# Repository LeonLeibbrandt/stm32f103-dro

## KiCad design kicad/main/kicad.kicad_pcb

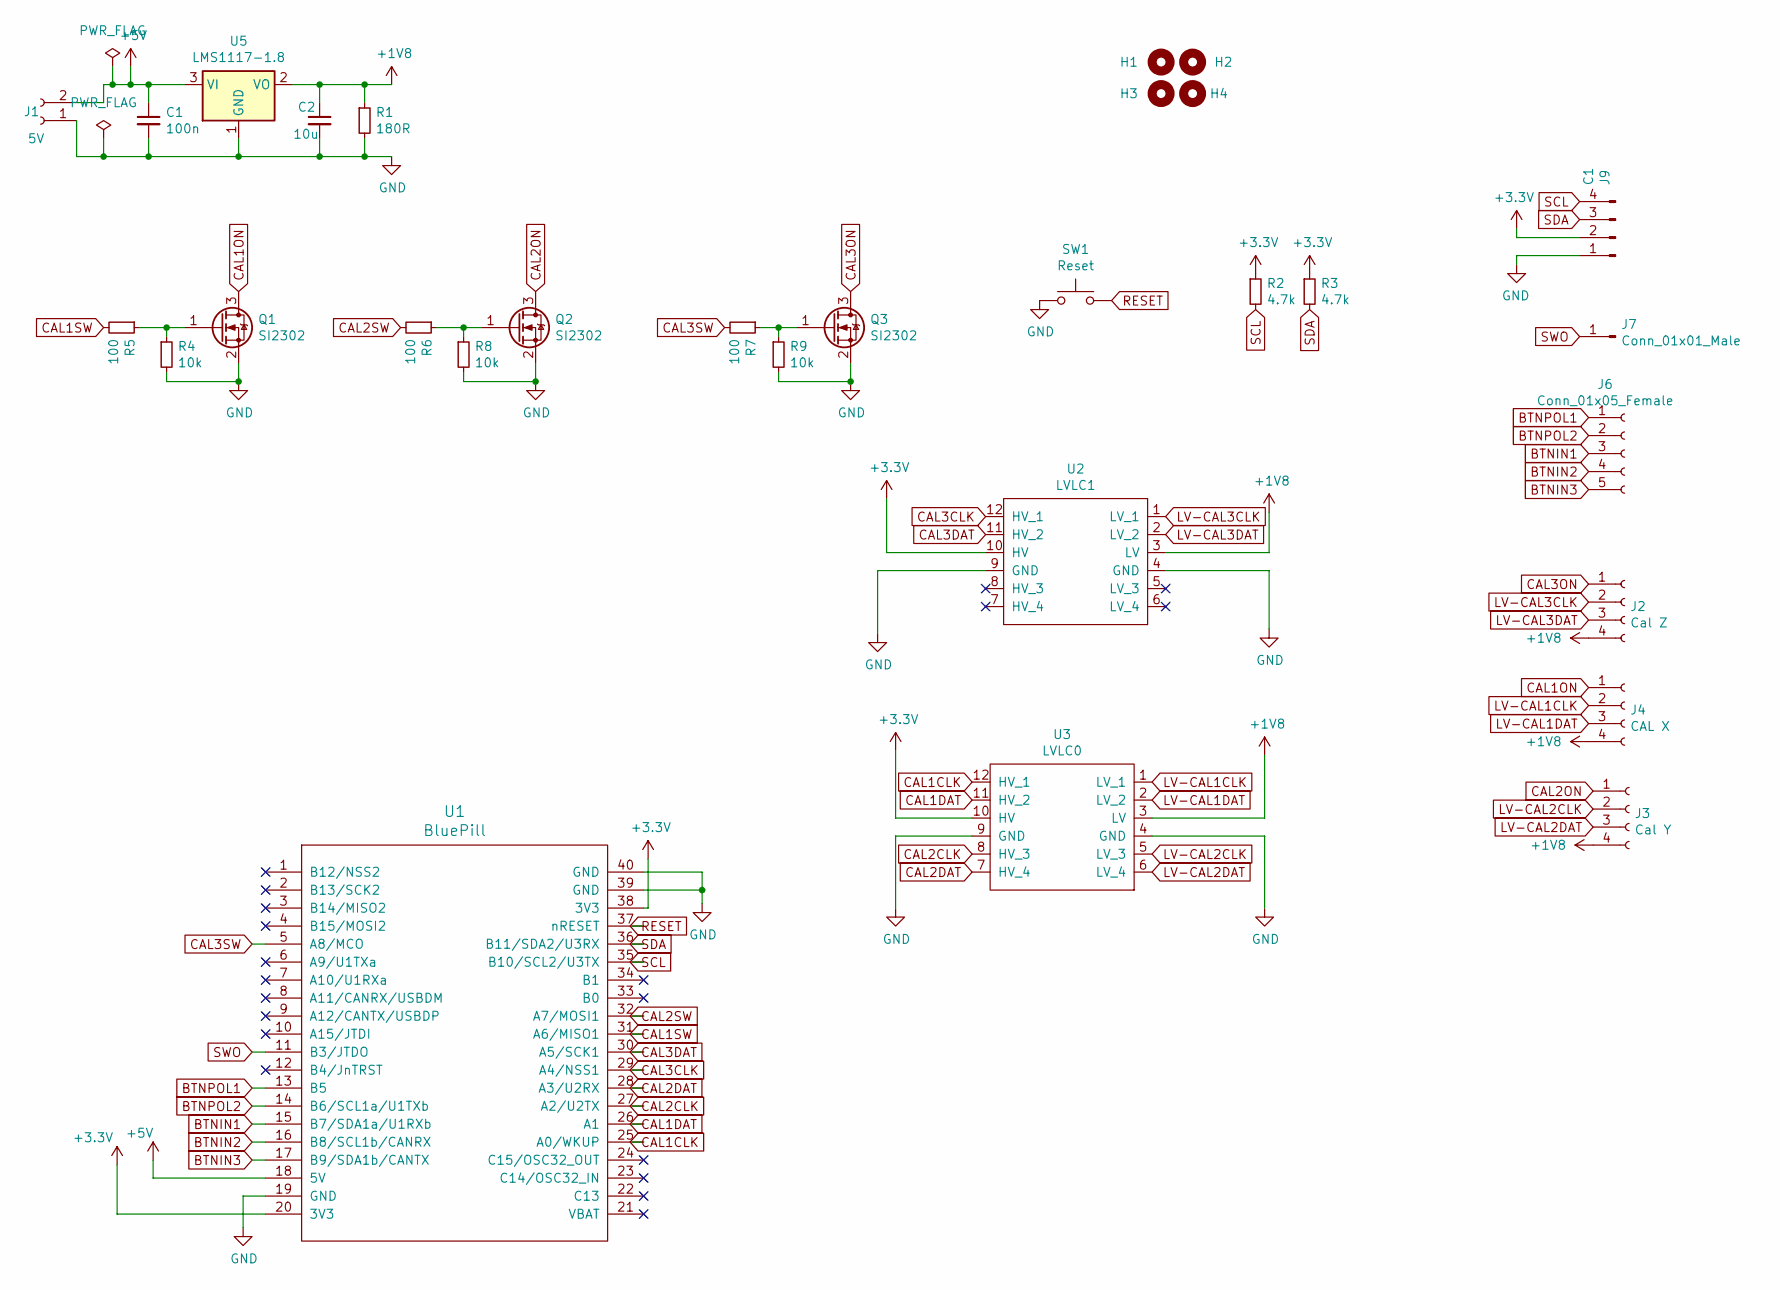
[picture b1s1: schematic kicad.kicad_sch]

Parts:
C1: 100n; C_1206_3216Metric
C2: 10u; C_1206_3216Metric
H1, H2, H3, H4: MountingHole; MountingHole_3.5mm_Pad
J1: 5V; JST_XH_B2B-XH-A_1x02_P2.50mm_Vertical
J2: Cal Z; JST_XH_B4B-XH-A_1x04_P2.50mm_Vertical
J3: Cal Y; JST_XH_B4B-XH-A_1x04_P2.50mm_Vertical
J4: CAL X; JST_XH_B4B-XH-A_1x04_P2.50mm_Vertical
J6: Conn_01x05_Female; JST_XH_B5B-XH-A_1x05_P2.50mm_Vertical
J7: Conn_01x01_Male; PinHeader_1x01_P2.54mm_Horizontal
J9: C1; JST_XH_B4B-XH-A_1x04_P2.50mm_Vertical
Q1, Q2, Q3: SI2302; SOT-23
R1: 180R; R_1206_3216Metric
R2, R3: 4.7k; R_1206_3216Metric
R4, R8, R9: 10k; R_1206_3216Metric
R5, R6, R7: 100; R_1206_3216Metric
SW1: Reset; PinHeader_1x02_P2.54mm_Vertical
U1: BluePill; bluepill
U2: LVLC1; levelconverter
U3: LVLC0; levelconverter
U5: LMS1117-1.8; SOT-223-3_TabPin2

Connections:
+1V8: C2.1, J2.4, J3.4, J4.4, R1.1, U2.3 (LV), U3.3 (LV), U5.2 (VO)
+3V3: J9.2, R2.1, R3.1, U1.20 (3V3), U1.38 (3V3), U2.10 (HV), U3.10 (HV)
+5V: C1.1, J1.2, U1.18 (5V), U5.3 (VI)
BTNIN1: J6.3, U1.15 (B7/SDA1a/U1RXb)
BTNIN2: J6.4, U1.16 (B8/SCL1b/CANRX)
BTNIN3: J6.5, U1.17 (B9/SDA1b/CANTX)
BTNPOL1: J6.1, U1.13 (B5)
BTNPOL2: J6.2, U1.14 (B6/SCL1a/U1TXb)
CAL1CLK: U1.25 (A0/WKUP), U3.12 (HV_1)
CAL1DAT: U1.26 (A1), U3.11 (HV_2)
CAL1ON: J4.1, Q1.3 (D)
CAL1SW: R5.2, U1.31 (A6/MISO1)
CAL2CLK: U1.27 (A2/U2TX), U3.8 (HV_3)
CAL2DAT: U1.28 (A3/U2RX), U3.7 (HV_4)
CAL2ON: J3.1, Q2.3 (D)
CAL2SW: R6.2, U1.32 (A7/MOSI1)
CAL3CLK: U1.29 (A4/NSS1), U2.12 (HV_1)
CAL3DAT: U1.30 (A5/SCK1), U2.11 (HV_2)
CAL3ON: J2.1, Q3.3 (D)
CAL3SW: R7.2, U1.5 (A8/MCO)
GND: C1.2, C2.2, J1.1, J9.1, Q1.2 (S), Q2.2 (S), Q3.2 (S), R1.2, R4.2, R8.2, R9.2, SW1.1, U1.19 (GND), U1.39 (GND), U1.40 (GND), U2.4 (GND), U2.9 (GND), U3.4 (GND), U3.9 (GND), U5.1 (GND)
LV-CAL1CLK: J4.2, U3.1 (LV_1)
LV-CAL1DAT: J4.3, U3.2 (LV_2)
LV-CAL2CLK: J3.2, U3.5 (LV_3)
LV-CAL2DAT: J3.3, U3.6 (LV_4)
LV-CAL3CLK: J2.2, U2.1 (LV_1)
LV-CAL3DAT: J2.3, U2.2 (LV_2)
unnamed: Q1.1 (G), R4.1, R5.1
unnamed: Q2.1 (G), R6.1, R8.1
unnamed: Q3.1 (G), R7.1, R9.1
RESET: SW1.2, U1.37 (nRESET)
SCL: J9.4, R2.2, U1.35 (B10/SCL2/U3TX)
SDA: J9.3, R3.2, U1.36 (B11/SDA2/U3RX)
SWO: J7.1, U1.11 (B3/JTDO)

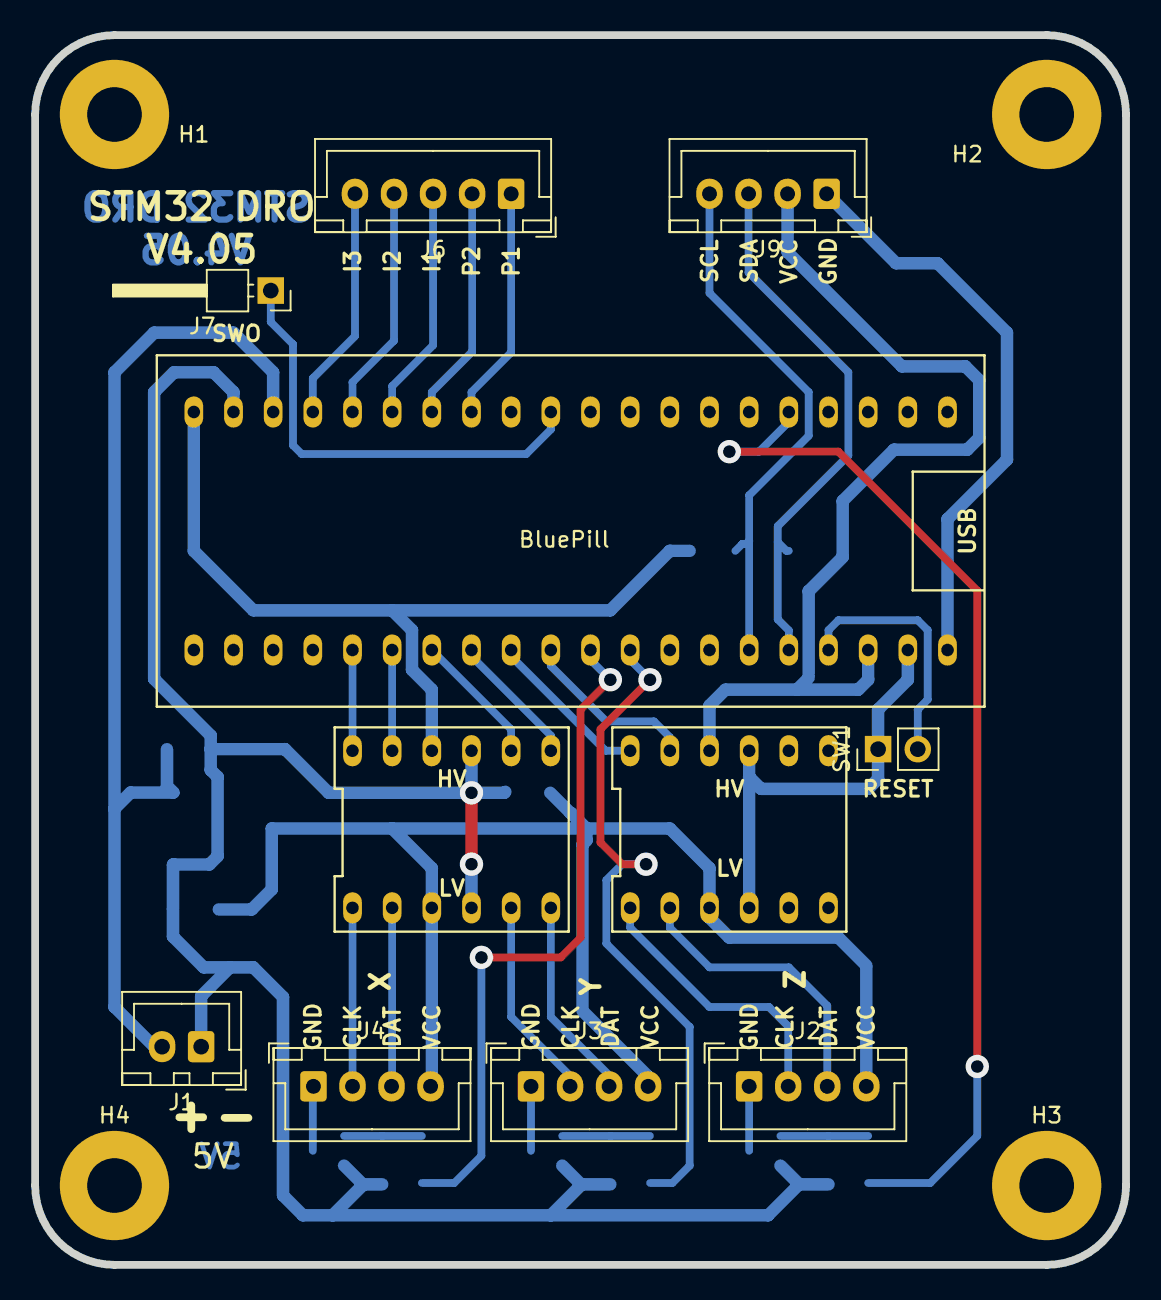
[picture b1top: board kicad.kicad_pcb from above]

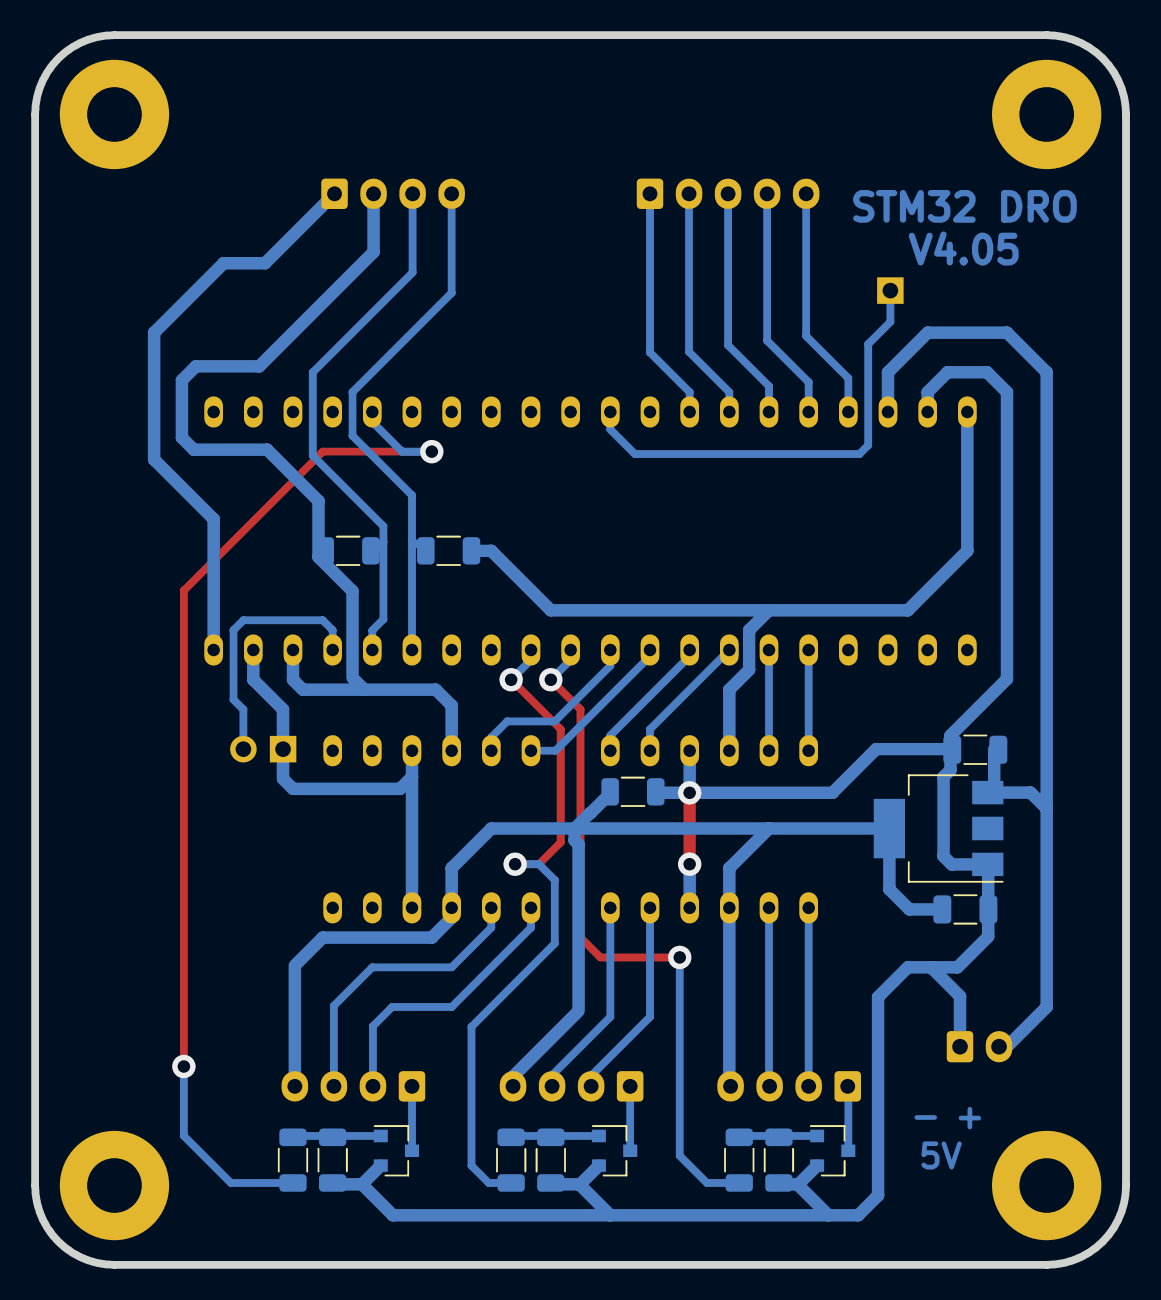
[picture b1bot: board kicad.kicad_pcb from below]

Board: 2 copper layers, 69.8 x 78.7 mm, 30 parts (15 on the bottom side), 34 nets.

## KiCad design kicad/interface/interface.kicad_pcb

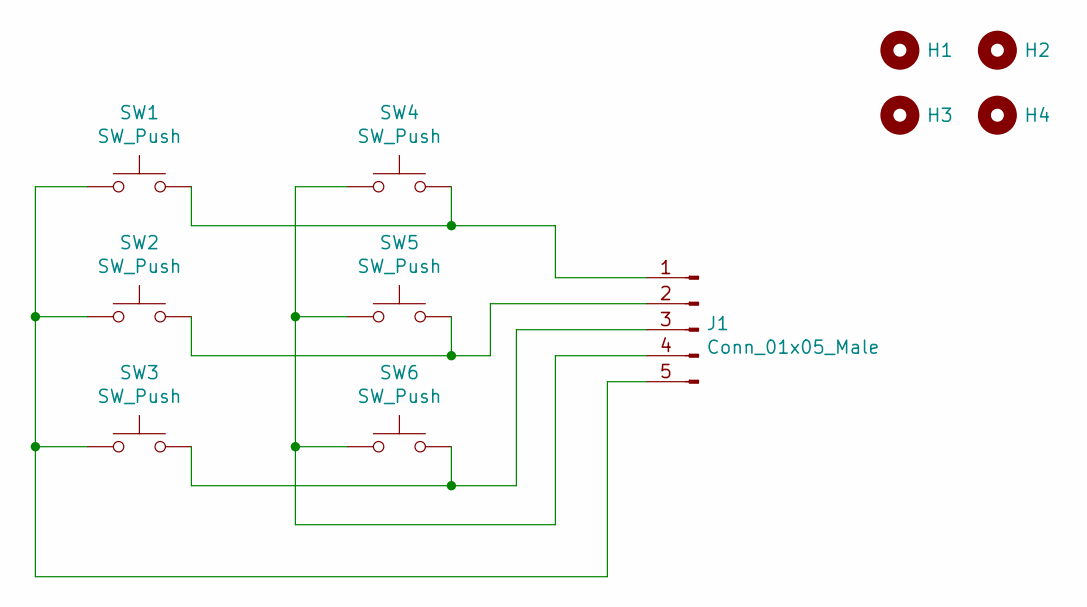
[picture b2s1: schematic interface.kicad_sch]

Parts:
H1, H2, H3, H4: MountingHole; MountingHole_3mm_Pad
J1: Conn_01x05_Male; JST_XH_B5B-XH-A_1x05_P2.50mm_Vertical
SW1, SW2, SW3, SW4, SW5, SW6: SW_Push; SW_PUSH-12mm

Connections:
unnamed: J1.1, SW1.2, SW4.2
unnamed: J1.2, SW2.2, SW5.2
unnamed: J1.3, SW3.2, SW6.2
unnamed: J1.4, SW4.1, SW5.1, SW6.1
unnamed: J1.5, SW1.1, SW2.1, SW3.1

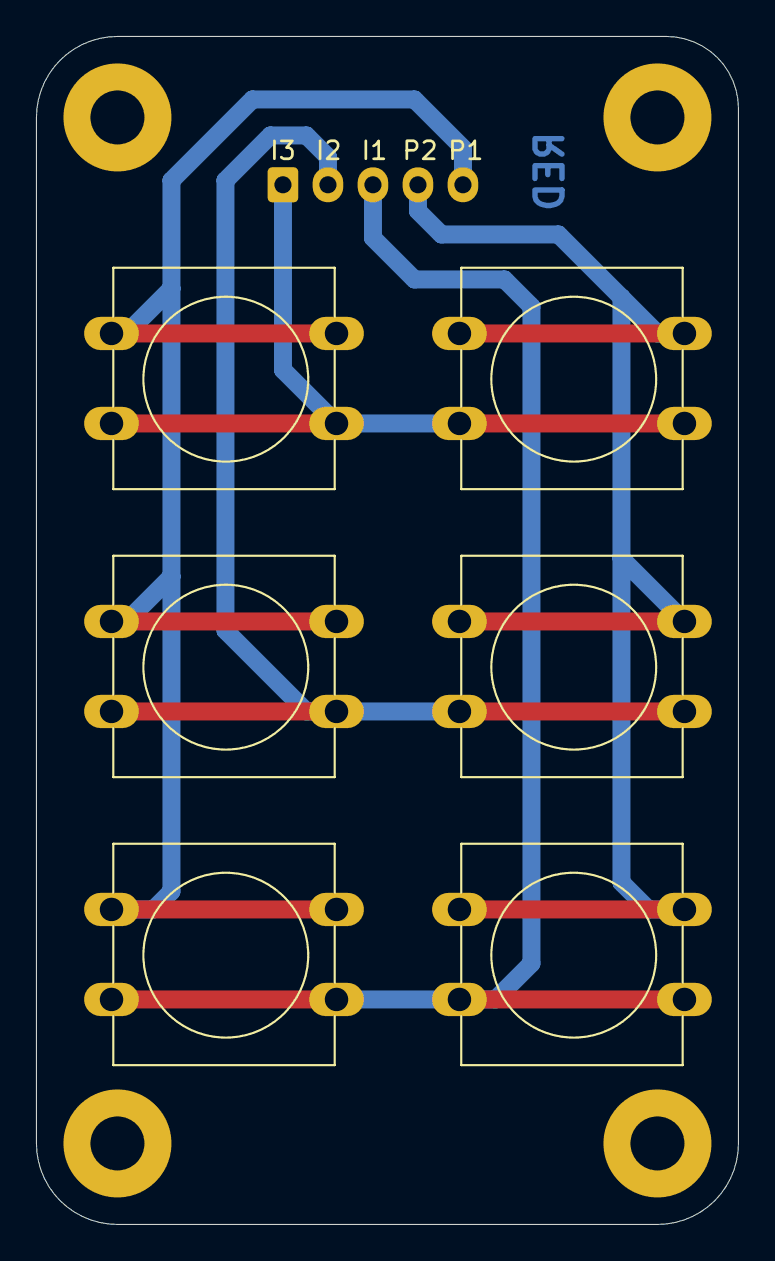
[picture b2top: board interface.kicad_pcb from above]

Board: 2 copper layers, 39.0 x 66.0 mm, 11 parts (1 on the bottom side), 5 nets.

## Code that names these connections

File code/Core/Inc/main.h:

/* USER CODE BEGIN Header */
/**
  ******************************************************************************
  * @file           : main.h
  * @brief          : Header for main.c file.
  *                   This file contains the common defines of the application.
  ******************************************************************************
  * @attention
  *
  * <h2><center>&copy; Copyright (c) 2020 STMicroelectronics.
  * All rights reserved.</center></h2>
  *
  * This software component is licensed by ST under BSD 3-Clause license,
  * the "License"; You may not use this file except in compliance with the
  * License. You may obtain a copy of the License at:
  *                        opensource.org/licenses/BSD-3-Clause
  *
  ******************************************************************************
  */
/* USER CODE END Header */

/* Define to prevent recursive inclusion -------------------------------------*/
#ifndef __MAIN_H
#define __MAIN_H

#ifdef __cplusplus
extern "C" {
#endif

/* Includes ------------------------------------------------------------------*/
#include "stm32f1xx_hal.h"

/* Private includes ----------------------------------------------------------*/
/* USER CODE BEGIN Includes */

/* USER CODE END Includes */

/* Exported types ------------------------------------------------------------*/
/* USER CODE BEGIN ET */

/* USER CODE END ET */

/* Exported constants --------------------------------------------------------*/
/* USER CODE BEGIN EC */

/* USER CODE END EC */

/* Exported macro ------------------------------------------------------------*/
/* USER CODE BEGIN EM */

/* USER CODE END EM */

/* Exported functions prototypes ---------------------------------------------*/
void Error_Handler(void);

/* USER CODE BEGIN EFP */

/* USER CODE END EFP */

/* Private defines -----------------------------------------------------------*/
#define LED_Pin GPIO_PIN_13
#define LED_GPIO_Port GPIOC
#define CAL0CLK_Pin GPIO_PIN_0
#define CAL0CLK_GPIO_Port GPIOA
#define CAL0CLK_EXTI_IRQn EXTI0_IRQn
#define CAL0DAT_Pin GPIO_PIN_1
#define CAL0DAT_GPIO_Port GPIOA
#define CAL1CLK_Pin GPIO_PIN_2
#define CAL1CLK_GPIO_Port GPIOA
#define CAL1CLK_EXTI_IRQn EXTI2_IRQn
#define CAL1DAT_Pin GPIO_PIN_3
#define CAL1DAT_GPIO_Port GPIOA
#define CAL2CLK_Pin GPIO_PIN_4
#define CAL2CLK_GPIO_Port GPIOA
#define CAL2CLK_EXTI_IRQn EXTI4_IRQn
#define CAL2DAT_Pin GPIO_PIN_5
#define CAL2DAT_GPIO_Port GPIOA
#define CAL1SW_Pin GPIO_PIN_6
#define CAL1SW_GPIO_Port GPIOA
#define CAL2SW_Pin GPIO_PIN_7
#define CAL2SW_GPIO_Port GPIOA
#define CAL3SW_Pin GPIO_PIN_8
#define CAL3SW_GPIO_Port GPIOA
#define BUTTOUT0_Pin GPIO_PIN_5
#define BUTTOUT0_GPIO_Port GPIOB
#define BUTTOUT1_Pin GPIO_PIN_6
#define BUTTOUT1_GPIO_Port GPIOB
#define BUTTIN0_Pin GPIO_PIN_7
#define BUTTIN0_GPIO_Port GPIOB
#define BUTTIN0_EXTI_IRQn EXTI9_5_IRQn
#define BUTTIN1_Pin GPIO_PIN_8
#define BUTTIN1_GPIO_Port GPIOB
#define BUTTIN1_EXTI_IRQn EXTI9_5_IRQn
#define BUTTIN2_Pin GPIO_PIN_9
#define BUTTIN2_GPIO_Port GPIOB
#define BUTTIN2_EXTI_IRQn EXTI9_5_IRQn

/* USER CODE BEGIN Private defines */

/* USER CODE END Private defines */

#ifdef __cplusplus
}
#endif

#endif /* __MAIN_H */

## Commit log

2022-05-27 Added 3d models for kicad
2022-11-13 Updated to CubeIDE 1.10.0
2024-09-24 Update With only STMCubeMX
